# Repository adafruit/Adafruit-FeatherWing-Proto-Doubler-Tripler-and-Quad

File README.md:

## FeatherWing Proto, Doubler, Tripler and Quad PCBs

<br/>
<br/>
<br/>
<br/>
&nbsp; 

Click the picture or one of the links below to purchase from the Adafruit shop

PCB files for the Adafruit Feather Wing Proto, Doubler, Tripler and Quad

Format is EagleCAD schematic and board layout 

Click to order the boards of your choice
 * FeatherWing Proto https://www.adafruit.com/products/2884
 * FeatherWing Doubler https://www.adafruit.com/products/2890
 * FeatherWing Tripler https://www.adafruit.com/products/3417
 * FeatherWing Quad 2x2 https://www.adafruit.com/product/4253
 * FeatherWing Quad Side by Side https://www.adafruit.com/product/4254

### Description

These are the FeatherWing Proto, Doubler, Tripler and Quad - prototyping add-ons for all Feather boards. Using our [Feather Stacking Headers](https://www.adafruit.com/products/2830) or [Feather Female Headers](http://www.adafruit.com/products/2886) you can connect a FeatherWing on top or bottom of your Feather board and let the board take flight! Additionally the Doubler and Tripler have Two and Three prototyping areas respectively. The magic of the Doubler and Tripler comes when stacking a Feather and another board on top of the one of them so you can work with both boards simultaneously side-by-side!

These boards havea duplicate breakouts for each pin on a Feather, as well as a bunch of plain grid proto holes. **For the Doubler, Triper and Quad the sets of Feather pins are cross connected** and For GND and 3.3V, we give you a strip of connected pads. There's plenty of room for [buttons](https://www.adafruit.com/categories/235), [indicator LEDs](https://www.adafruit.com/categories/90), or anything for your portable project. The FeatherWing Proto, Doubler, Tripler and Quad make ideal partners for any of our Feather boards.

In addition to the PCB, the Doubler, Tripler and Quad come with 

* Doubler
	* 1 set [Feather Stacking Headers (you can cut these down after soldering so they aren't stacking-style if you want a slimmer build)](https://www.adafruit.com/products/2830)
	* 1 set [Feather Female Headers](http://www.adafruit.com/products/2886)

* Tripler
	* 3 sets Feather Female Headers

* Quad
    * 4 sets Feather Female Headers

**You'll need to solder on the headers to the PCB**, the Doubler, Tripler and Quad come as mini kits!

[Check out our range of Feather boards here.](https://www.adafruit.com/feather)

### License

Adafruit invests time and resources providing this open source design, please support Adafruit and open-source hardware by purchasing products from [Adafruit](https://www.adafruit.com)!

Designed by Limor Fried/Ladyada for Adafruit Industries.

Creative Commons Attribution/Share-Alike, all text above must be included in any redistribution. See license.txt for additional details.

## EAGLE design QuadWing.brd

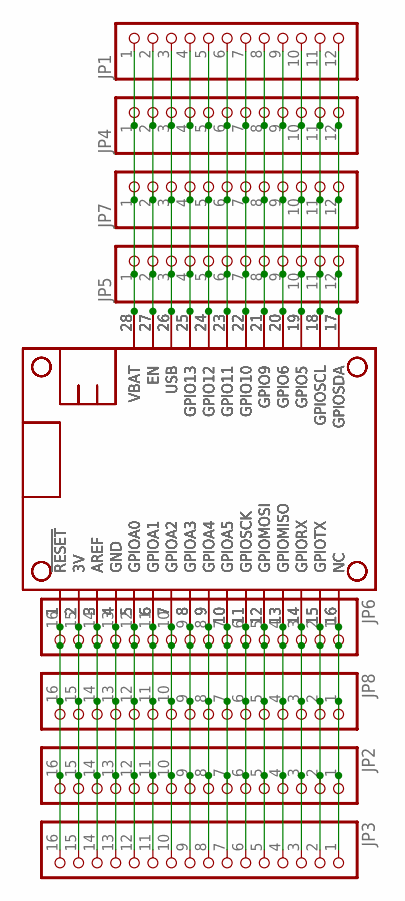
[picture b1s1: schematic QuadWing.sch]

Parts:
JP1, JP4, JP5, JP7: HEADER-1X1276MIL; 1X12_ROUND_76MIL
JP2, JP3, JP6, JP8: HEADER-1X16_76MIL; 1X16_ROUND_76MIL
MS1, MS2, MS3, MS4: FEATHERWING_NODIM; FEATHERWING_DIM

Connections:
3V: JP2.15, JP3.15, JP6.15, JP8.15, MS1.2 (3V), MS2.2 (3V), MS3.2 (3V), MS4.2 (3V)
A: JP2.12, JP3.12, JP6.12, JP8.12, MS1.5 (GPIOA0), MS2.5 (GPIOA0), MS3.5 (GPIOA0), MS4.5 (GPIOA0)
AREF: JP2.14, JP3.14, JP6.14, JP8.14, MS1.3 (AREF), MS2.3 (AREF), MS3.3 (AREF), MS4.3 (AREF)
B: JP2.11, JP3.11, JP6.11, JP8.11, MS1.6 (GPIOA1), MS2.6 (GPIOA1), MS3.6 (GPIOA1), MS4.6 (GPIOA1)
C: JP2.10, JP3.10, JP6.10, JP8.10, MS1.7 (GPIOA2), MS2.7 (GPIOA2), MS3.7 (GPIOA2), MS4.7 (GPIOA2)
D: JP2.9, JP3.9, JP6.9, JP8.9, MS1.8 (GPIOA3), MS2.8 (GPIOA3), MS3.8 (GPIOA3), MS4.8 (GPIOA3)
E: JP2.8, JP3.8, JP6.8, JP8.8, MS1.9 (GPIOA4), MS2.9 (GPIOA4), MS3.9 (GPIOA4), MS4.9 (GPIOA4)
EN: JP1.2, JP4.2, JP5.2, JP7.2, MS1.27 (EN), MS2.27 (EN), MS3.27 (EN), MS4.27 (EN)
F: JP2.7, JP3.7, JP6.7, JP8.7, MS1.10 (GPIOA5), MS2.10 (GPIOA5), MS3.10 (GPIOA5), MS4.10 (GPIOA5)
G: JP2.1, JP3.1, JP6.1, JP8.1, MS1.16 (NC), MS2.16 (NC), MS3.16 (NC), MS4.16 (NC)
GND: JP2.13, JP3.13, JP6.13, JP8.13, MS1.4 (GND), MS2.4 (GND), MS3.4 (GND), MS4.4 (GND)
I: JP1.9, JP4.9, JP5.9, JP7.9, MS1.20 (GPIO6), MS2.20 (GPIO6), MS3.20 (GPIO6), MS4.20 (GPIO6)
J: JP1.10, JP4.10, JP5.10, JP7.10, MS1.19 (GPIO5), MS2.19 (GPIO5), MS3.19 (GPIO5), MS4.19 (GPIO5)
K: JP1.8, JP4.8, JP5.8, JP7.8, MS1.21 (GPIO9), MS2.21 (GPIO9), MS3.21 (GPIO9), MS4.21 (GPIO9)
L: JP1.7, JP4.7, JP5.7, JP7.7, MS1.22 (GPIO10), MS2.22 (GPIO10), MS3.22 (GPIO10), MS4.22 (GPIO10)
M: JP1.6, JP4.6, JP5.6, JP7.6, MS1.23 (GPIO11), MS2.23 (GPIO11), MS3.23 (GPIO11), MS4.23 (GPIO11)
MISO: JP2.4, JP3.4, JP6.4, JP8.4, MS1.13 (GPIOMISO), MS2.13 (GPIOMISO), MS3.13 (GPIOMISO), MS4.13 (GPIOMISO)
MOSI: JP2.5, JP3.5, JP6.5, JP8.5, MS1.12 (GPIOMOSI), MS2.12 (GPIOMOSI), MS3.12 (GPIOMOSI), MS4.12 (GPIOMOSI)
N: JP1.5, JP4.5, JP5.5, JP7.5, MS1.24 (GPIO12), MS2.24 (GPIO12), MS3.24 (GPIO12), MS4.24 (GPIO12)
O: JP1.4, JP4.4, JP5.4, JP7.4, MS1.25 (GPIO13), MS2.25 (GPIO13), MS3.25 (GPIO13), MS4.25 (GPIO13)
RESET: JP2.16, JP3.16, JP6.16, JP8.16, MS1.1 (!RESET), MS2.1 (!RESET), MS3.1 (!RESET), MS4.1 (!RESET)
RX: JP2.3, JP3.3, JP6.3, JP8.3, MS1.14 (GPIORX), MS2.14 (GPIORX), MS3.14 (GPIORX), MS4.14 (GPIORX)
SCK: JP2.6, JP3.6, JP6.6, JP8.6, MS1.11 (GPIOSCK), MS2.11 (GPIOSCK), MS3.11 (GPIOSCK), MS4.11 (GPIOSCK)
SCL: JP1.11, JP4.11, JP5.11, JP7.11, MS1.18 (GPIOSCL), MS2.18 (GPIOSCL), MS3.18 (GPIOSCL), MS4.18 (GPIOSCL)
SDA: JP1.12, JP4.12, JP5.12, JP7.12, MS1.17 (GPIOSDA), MS2.17 (GPIOSDA), MS3.17 (GPIOSDA), MS4.17 (GPIOSDA)
TX: JP2.2, JP3.2, JP6.2, JP8.2, MS1.15 (GPIOTX), MS2.15 (GPIOTX), MS3.15 (GPIOTX), MS4.15 (GPIOTX)
USB: JP1.3, JP4.3, JP5.3, JP7.3, MS1.26 (USB), MS2.26 (USB), MS3.26 (USB), MS4.26 (USB)
VBAT: JP1.1, JP4.1, JP5.1, JP7.1, MS1.28 (VBAT), MS2.28 (VBAT), MS3.28 (VBAT), MS4.28 (VBAT)

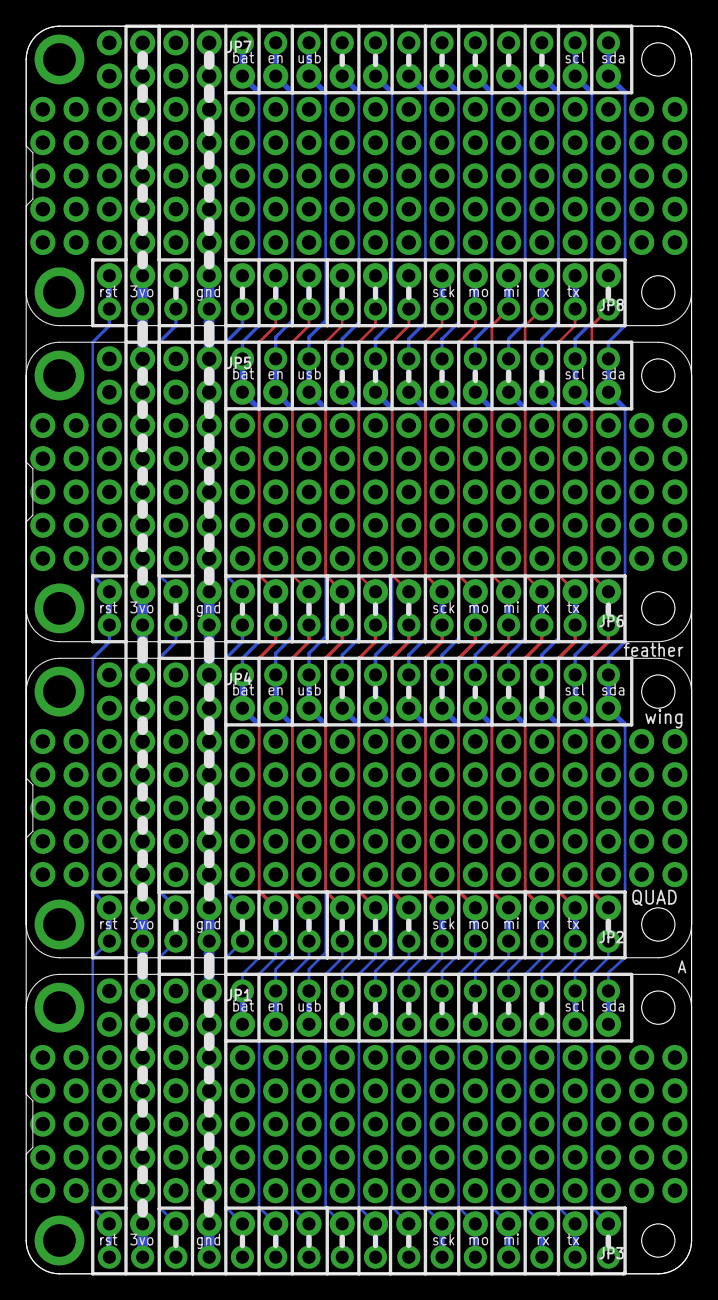
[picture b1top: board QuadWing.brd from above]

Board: 2 copper layers, 50.8 x 95.2 mm, 12 parts (0 on the bottom side), 28 nets.

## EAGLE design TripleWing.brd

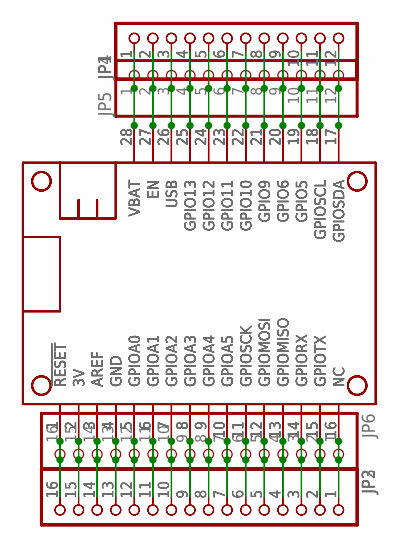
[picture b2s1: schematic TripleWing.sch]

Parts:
JP1, JP4, JP5: HEADER-1X1276MIL; 1X12_ROUND_76MIL
JP2, JP3, JP6: HEADER-1X16_76MIL; 1X16_ROUND_76MIL
MS1, MS2, MS3: FEATHERWING_NODIM; FEATHERWING_DIM

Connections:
3V: JP2.15, JP3.15, JP6.15, MS1.2 (3V), MS2.2 (3V), MS3.2 (3V)
A: JP2.12, JP3.12, JP6.12, MS1.5 (GPIOA0), MS2.5 (GPIOA0), MS3.5 (GPIOA0)
AREF: JP2.14, JP3.14, JP6.14, MS1.3 (AREF), MS2.3 (AREF), MS3.3 (AREF)
B: JP2.11, JP3.11, JP6.11, MS1.6 (GPIOA1), MS2.6 (GPIOA1), MS3.6 (GPIOA1)
C: JP2.10, JP3.10, JP6.10, MS1.7 (GPIOA2), MS2.7 (GPIOA2), MS3.7 (GPIOA2)
D: JP2.9, JP3.9, JP6.9, MS1.8 (GPIOA3), MS2.8 (GPIOA3), MS3.8 (GPIOA3)
E: JP2.8, JP3.8, JP6.8, MS1.9 (GPIOA4), MS2.9 (GPIOA4), MS3.9 (GPIOA4)
EN: JP1.2, JP4.2, JP5.2, MS1.27 (EN), MS2.27 (EN), MS3.27 (EN)
F: JP2.7, JP3.7, JP6.7, MS1.10 (GPIOA5), MS2.10 (GPIOA5), MS3.10 (GPIOA5)
G: JP2.1, JP3.1, JP6.1, MS1.16 (NC), MS2.16 (NC), MS3.16 (NC)
GND: JP2.13, JP3.13, JP6.13, MS1.4 (GND), MS2.4 (GND), MS3.4 (GND)
I: JP1.9, JP4.9, JP5.9, MS1.20 (GPIO6), MS2.20 (GPIO6), MS3.20 (GPIO6)
J: JP1.10, JP4.10, JP5.10, MS1.19 (GPIO5), MS2.19 (GPIO5), MS3.19 (GPIO5)
K: JP1.8, JP4.8, JP5.8, MS1.21 (GPIO9), MS2.21 (GPIO9), MS3.21 (GPIO9)
L: JP1.7, JP4.7, JP5.7, MS1.22 (GPIO10), MS2.22 (GPIO10), MS3.22 (GPIO10)
M: JP1.6, JP4.6, JP5.6, MS1.23 (GPIO11), MS2.23 (GPIO11), MS3.23 (GPIO11)
MISO: JP2.4, JP3.4, JP6.4, MS1.13 (GPIOMISO), MS2.13 (GPIOMISO), MS3.13 (GPIOMISO)
MOSI: JP2.5, JP3.5, JP6.5, MS1.12 (GPIOMOSI), MS2.12 (GPIOMOSI), MS3.12 (GPIOMOSI)
N: JP1.5, JP4.5, JP5.5, MS1.24 (GPIO12), MS2.24 (GPIO12), MS3.24 (GPIO12)
O: JP1.4, JP4.4, JP5.4, MS1.25 (GPIO13), MS2.25 (GPIO13), MS3.25 (GPIO13)
RESET: JP2.16, JP3.16, JP6.16, MS1.1 (!RESET), MS2.1 (!RESET), MS3.1 (!RESET)
RX: JP2.3, JP3.3, JP6.3, MS1.14 (GPIORX), MS2.14 (GPIORX), MS3.14 (GPIORX)
SCK: JP2.6, JP3.6, JP6.6, MS1.11 (GPIOSCK), MS2.11 (GPIOSCK), MS3.11 (GPIOSCK)
SCL: JP1.11, JP4.11, JP5.11, MS1.18 (GPIOSCL), MS2.18 (GPIOSCL), MS3.18 (GPIOSCL)
SDA: JP1.12, JP4.12, JP5.12, MS1.17 (GPIOSDA), MS2.17 (GPIOSDA), MS3.17 (GPIOSDA)
TX: JP2.2, JP3.2, JP6.2, MS1.15 (GPIOTX), MS2.15 (GPIOTX), MS3.15 (GPIOTX)
USB: JP1.3, JP4.3, JP5.3, MS1.26 (USB), MS2.26 (USB), MS3.26 (USB)
VBAT: JP1.1, JP4.1, JP5.1, MS1.28 (VBAT), MS2.28 (VBAT), MS3.28 (VBAT)

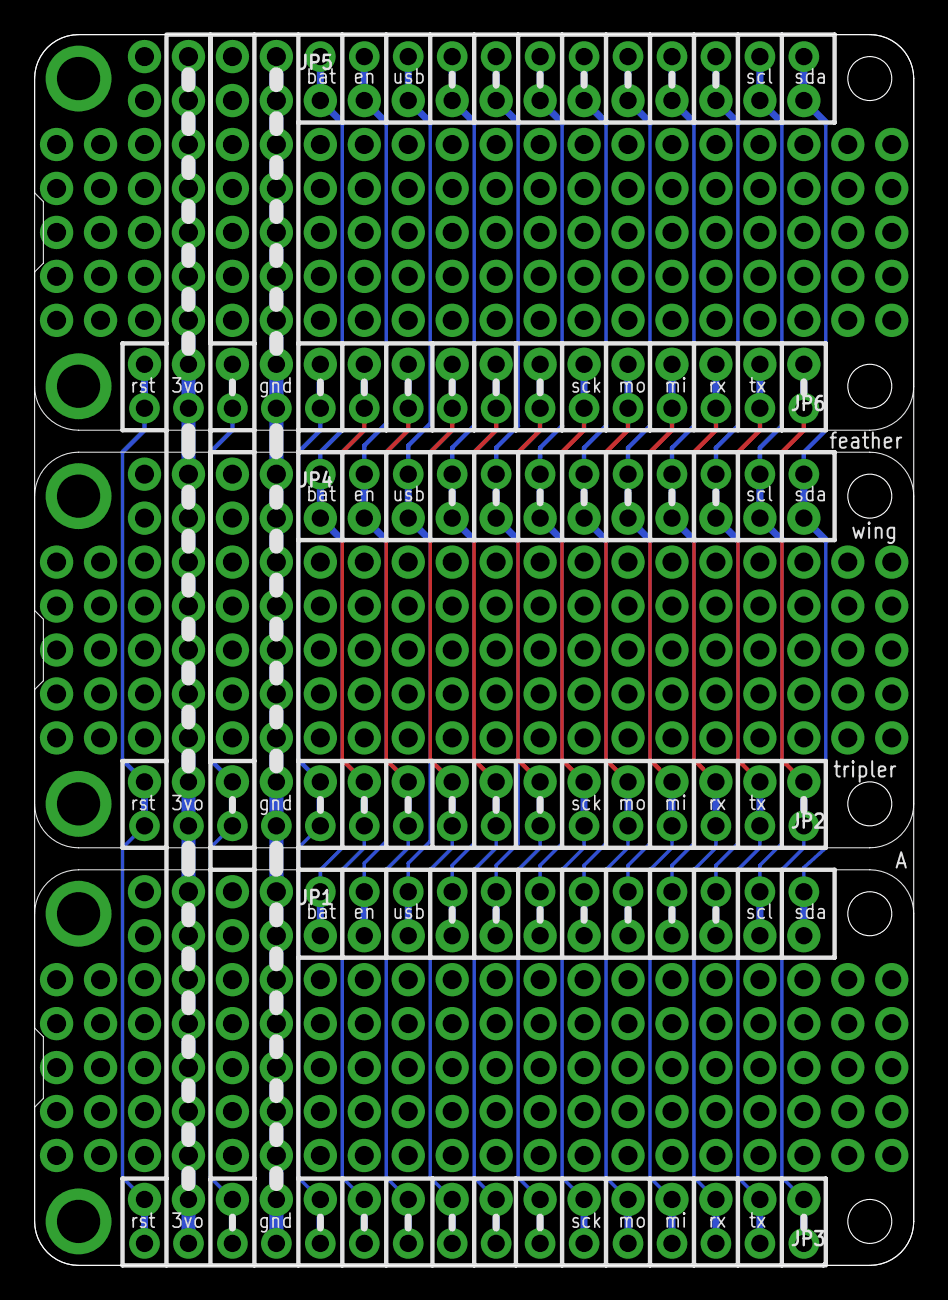
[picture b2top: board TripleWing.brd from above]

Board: 2 copper layers, 50.8 x 71.1 mm, 9 parts (0 on the bottom side), 28 nets.

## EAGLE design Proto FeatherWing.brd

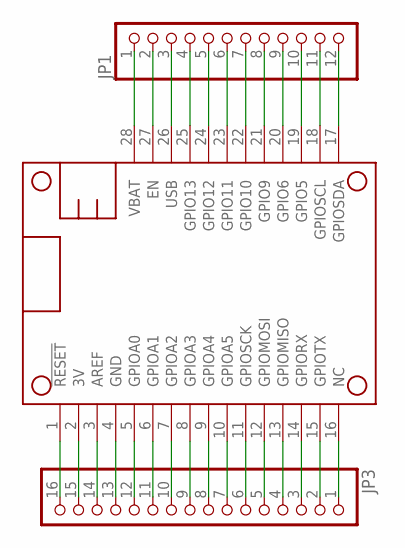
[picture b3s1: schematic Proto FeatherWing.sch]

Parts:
JP1: HEADER-1X1276MIL; 1X12_ROUND_76MIL
JP3: HEADER-1X16_76MIL; 1X16_ROUND_76MIL
MS1: FEATHERWING

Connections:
3V: JP3.15, MS1.2 (3V)
AREF: JP3.14, MS1.3 (AREF)
GND: JP3.13, MS1.4 (GND)
unnamed: JP1.2, MS1.27 (EN)
unnamed: JP3.1, MS1.16 (NC)
unnamed: JP1.4, MS1.25 (GPIO13)
unnamed: JP3.2, MS1.15 (GPIOTX)
unnamed: JP1.5, MS1.24 (GPIO12)
unnamed: JP3.3, MS1.14 (GPIORX)
unnamed: JP3.4, MS1.13 (GPIOMISO)
unnamed: JP3.5, MS1.12 (GPIOMOSI)
unnamed: JP3.6, MS1.11 (GPIOSCK)
unnamed: JP3.7, MS1.10 (GPIOA5)
unnamed: JP3.8, MS1.9 (GPIOA4)
unnamed: JP3.9, MS1.8 (GPIOA3)
unnamed: JP3.10, MS1.7 (GPIOA2)
unnamed: JP3.11, MS1.6 (GPIOA1)
unnamed: JP3.12, MS1.5 (GPIOA0)
unnamed: JP3.16, MS1.1 (!RESET)
unnamed: JP1.6, MS1.23 (GPIO11)
unnamed: JP1.7, MS1.22 (GPIO10)
unnamed: JP1.8, MS1.21 (GPIO9)
unnamed: JP1.9, MS1.20 (GPIO6)
unnamed: JP1.10, MS1.19 (GPIO5)
unnamed: JP1.11, MS1.18 (GPIOSCL)
unnamed: JP1.12, MS1.17 (GPIOSDA)
USB: JP1.3, MS1.26 (USB)
VBAT: JP1.1, MS1.28 (VBAT)

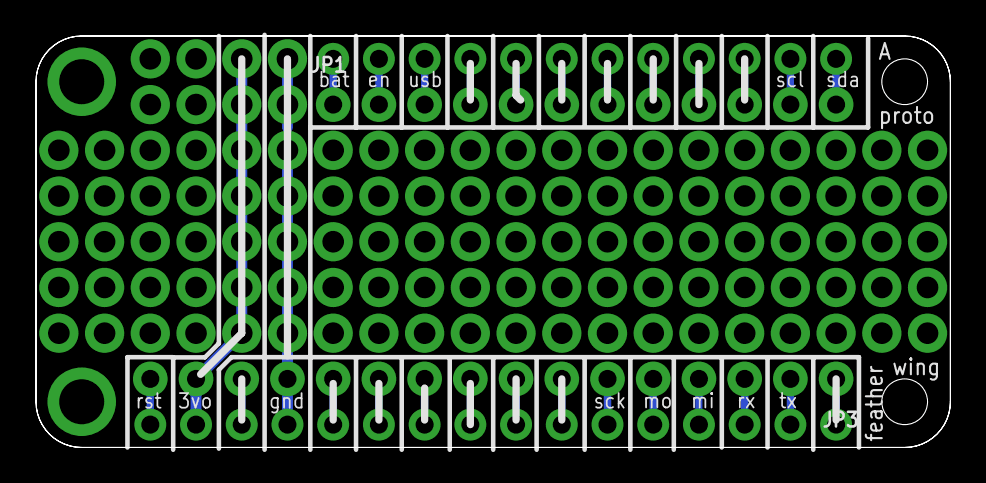
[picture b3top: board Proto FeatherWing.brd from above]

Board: 2 copper layers, 50.8 x 22.9 mm, 3 parts (0 on the bottom side), 28 nets.

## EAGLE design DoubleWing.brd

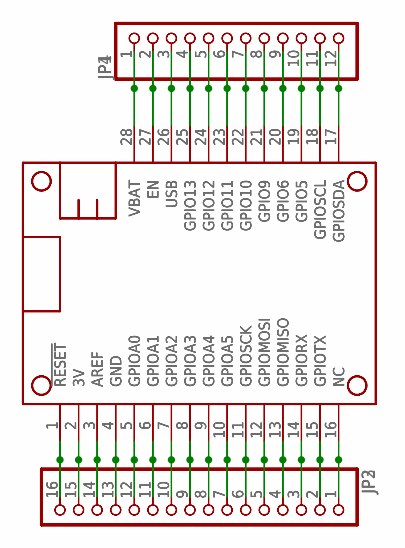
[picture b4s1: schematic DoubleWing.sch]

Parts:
JP1, JP4: HEADER-1X1276MIL; 1X12_ROUND_76MIL
JP2, JP3: HEADER-1X16_76MIL; 1X16_ROUND_76MIL
MS1, MS2: FEATHERWING_NODIM; FEATHERWING_DIM

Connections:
3V: JP2.15, JP3.15, MS1.2 (3V), MS2.2 (3V)
GND: JP2.13, JP3.13, MS1.4 (GND), MS2.4 (GND)
unnamed: JP1.2, JP4.2, MS1.27 (EN), MS2.27 (EN)
unnamed: JP2.1, JP3.1, MS1.16 (NC), MS2.16 (NC)
unnamed: JP1.4, JP4.4, MS1.25 (GPIO13), MS2.25 (GPIO13)
unnamed: JP2.2, JP3.2, MS1.15 (GPIOTX), MS2.15 (GPIOTX)
unnamed: JP1.5, JP4.5, MS1.24 (GPIO12), MS2.24 (GPIO12)
unnamed: JP2.3, JP3.3, MS1.14 (GPIORX), MS2.14 (GPIORX)
unnamed: JP2.4, JP3.4, MS1.13 (GPIOMISO), MS2.13 (GPIOMISO)
unnamed: JP2.5, JP3.5, MS1.12 (GPIOMOSI), MS2.12 (GPIOMOSI)
unnamed: JP2.6, JP3.6, MS1.11 (GPIOSCK), MS2.11 (GPIOSCK)
unnamed: JP2.7, JP3.7, MS1.10 (GPIOA5), MS2.10 (GPIOA5)
unnamed: JP2.8, JP3.8, MS1.9 (GPIOA4), MS2.9 (GPIOA4)
unnamed: JP2.9, JP3.9, MS1.8 (GPIOA3), MS2.8 (GPIOA3)
unnamed: JP2.10, JP3.10, MS1.7 (GPIOA2), MS2.7 (GPIOA2)
unnamed: JP2.11, JP3.11, MS1.6 (GPIOA1), MS2.6 (GPIOA1)
unnamed: JP2.12, JP3.12, MS1.5 (GPIOA0), MS2.5 (GPIOA0)
unnamed: JP2.14, JP3.14, MS1.3 (AREF), MS2.3 (AREF)
unnamed: JP2.16, JP3.16, MS1.1 (!RESET), MS2.1 (!RESET)
unnamed: JP1.6, JP4.6, MS1.23 (GPIO11), MS2.23 (GPIO11)
unnamed: JP1.7, JP4.7, MS1.22 (GPIO10), MS2.22 (GPIO10)
unnamed: JP1.8, JP4.8, MS1.21 (GPIO9), MS2.21 (GPIO9)
unnamed: JP1.9, JP4.9, MS1.20 (GPIO6), MS2.20 (GPIO6)
unnamed: JP1.10, JP4.10, MS1.19 (GPIO5), MS2.19 (GPIO5)
unnamed: JP1.11, JP4.11, MS1.18 (GPIOSCL), MS2.18 (GPIOSCL)
unnamed: JP1.12, JP4.12, MS1.17 (GPIOSDA), MS2.17 (GPIOSDA)
USB: JP1.3, JP4.3, MS1.26 (USB), MS2.26 (USB)
VBAT: JP1.1, JP4.1, MS1.28 (VBAT), MS2.28 (VBAT)

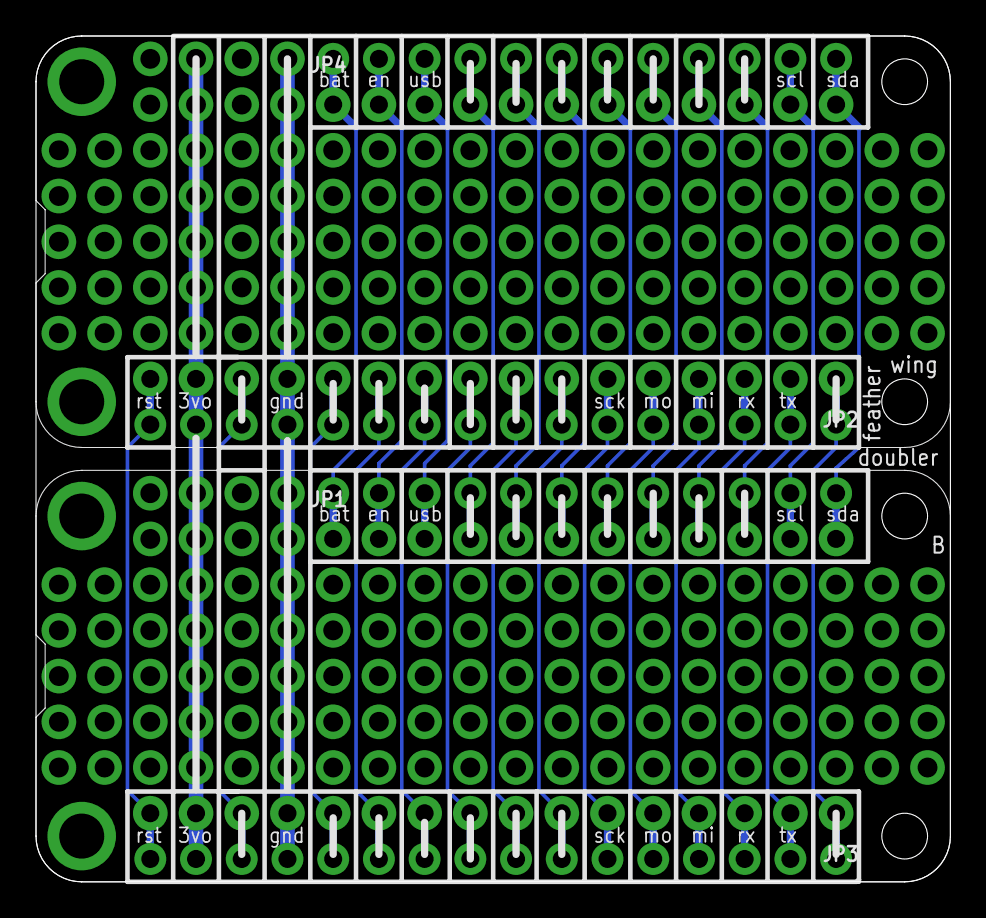
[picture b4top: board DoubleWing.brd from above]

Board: 2 copper layers, 50.8 x 47.0 mm, 6 parts (0 on the bottom side), 28 nets.

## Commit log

2016-01-07 PCBs
2016-01-07 add urls
2016-04-22 fix minor hole location error - EN is now labeled EN
2017-04-02 tripler
2017-04-02 add url
2019-07-17 updated to use cookiecutter for pcb repos
2019-07-17 README fixed
2019-07-17 one more small README fix
2019-11-01 Adding quad files.
2019-11-01 README title fix
